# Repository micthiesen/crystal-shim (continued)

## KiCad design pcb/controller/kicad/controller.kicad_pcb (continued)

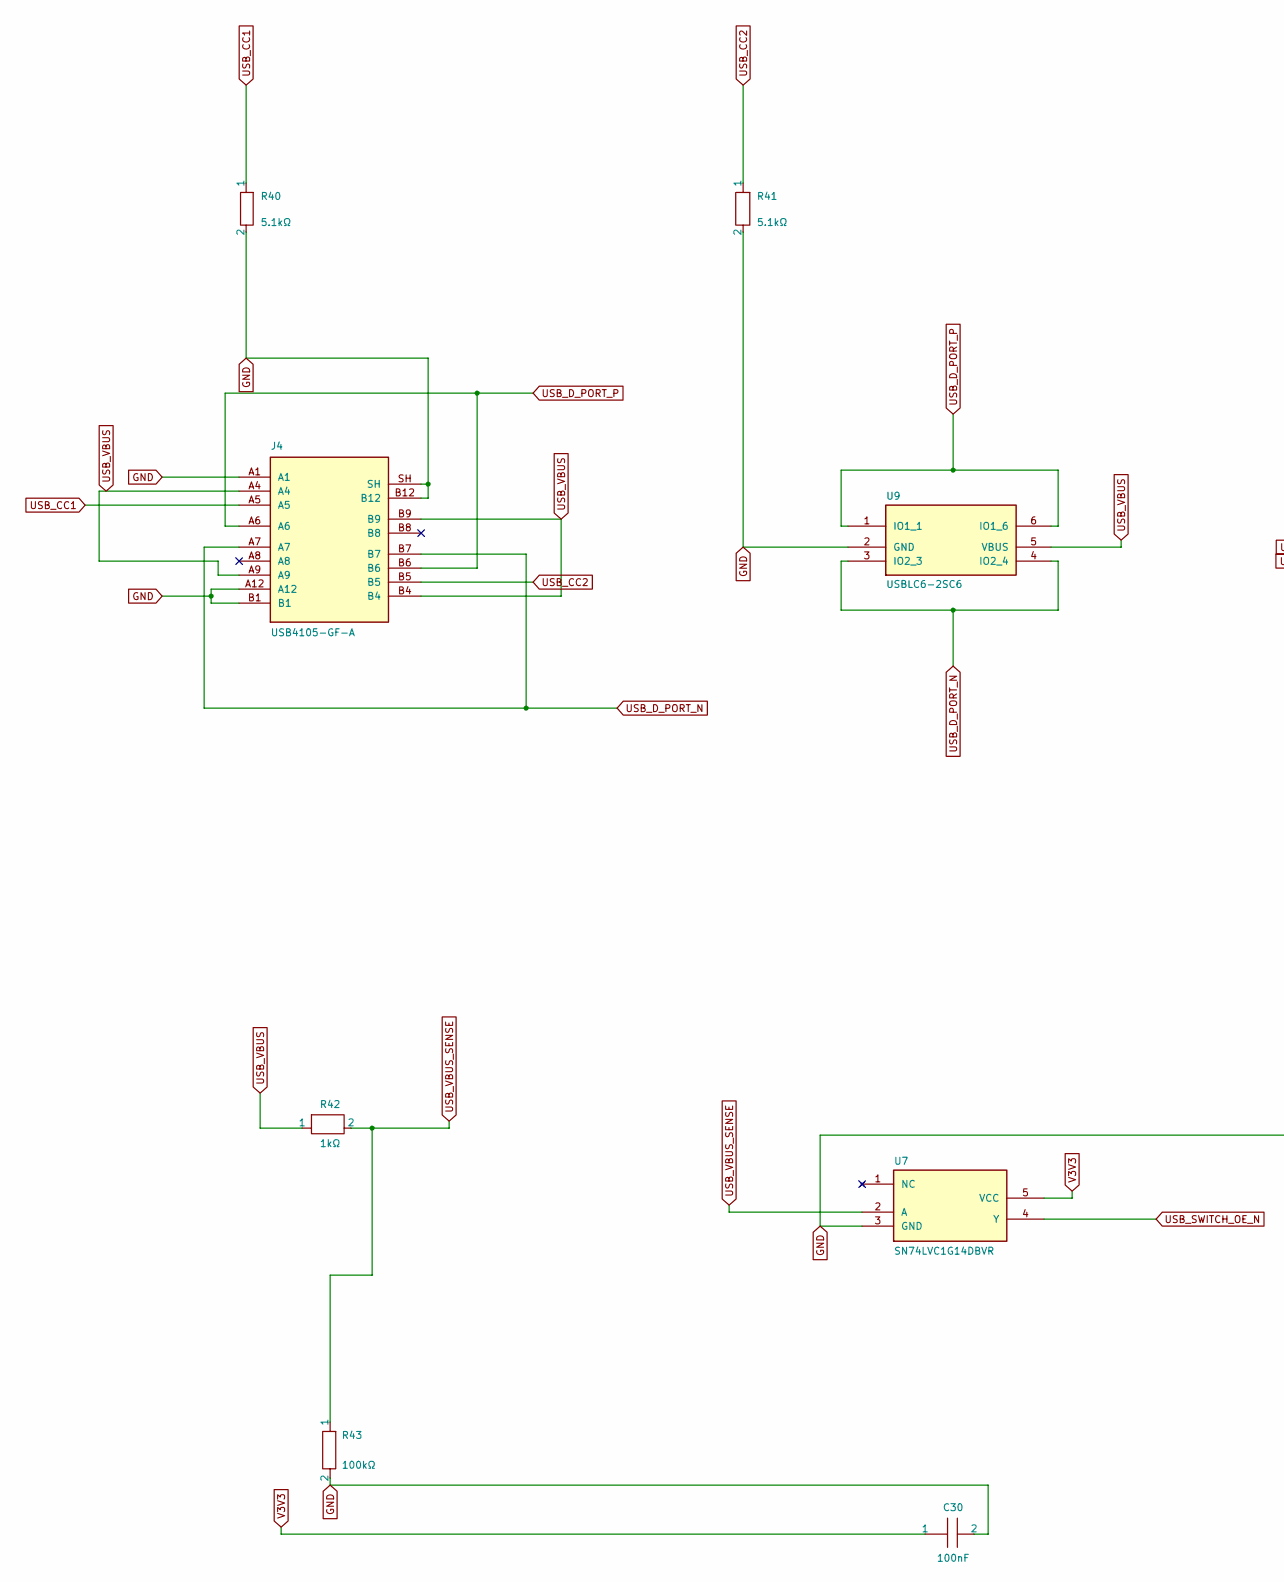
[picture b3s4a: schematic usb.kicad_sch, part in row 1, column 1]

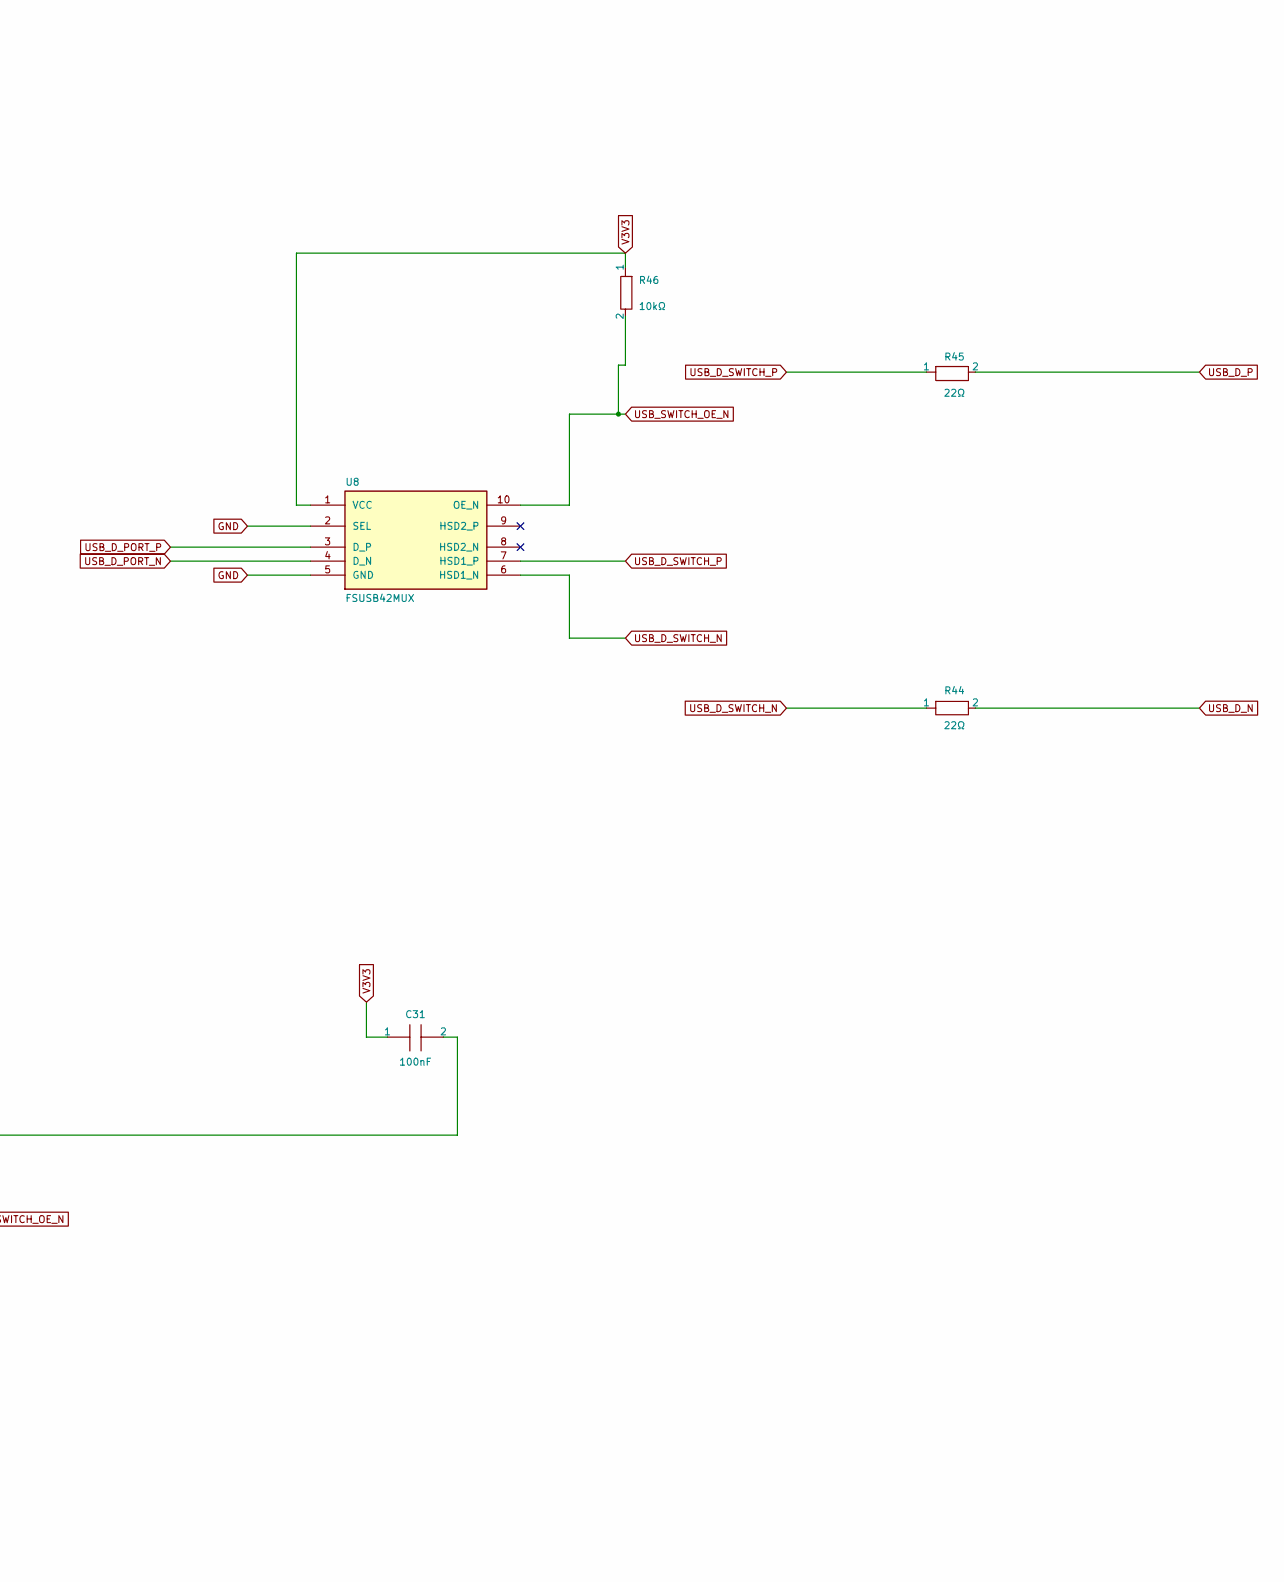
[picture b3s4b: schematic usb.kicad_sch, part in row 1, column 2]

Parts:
C30: 100nF; Controller_C30; MPN C1608X7R1H104K080AA
C31: 100nF; Controller_C31; MPN C1608X7R1H104K080AA
J4: USB4105-GF-A; Controller_J4; MPN USB4105-GF-A
R40: 5.1kΩ; Controller_R40; MPN ERJ3EKF5101V
R41: 5.1kΩ; Controller_R41; MPN ERJ3EKF5101V
R42: 1kΩ; Controller_R42; MPN ERJ3EKF1001V
R43: 100kΩ; Controller_R43; MPN ERJ3EKF1003V
R44: 22Ω; Controller_R44; MPN ERJ3EKF22R0V
R45: 22Ω; Controller_R45; MPN ERJ3EKF22R0V
R46: 10kΩ; Controller_R46; MPN ERJ3EKF1002V
U7: SN74LVC1G14DBVR; Controller_U7; MPN SN74LVC1G14DBVR
U8: FSUSB42MUX; Controller_U8; MPN FSUSB42MUX
U9: USBLC6-2SC6; Controller_U9; MPN USBLC6-2SC6

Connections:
GND: C30.2, C31.2, J4.A1, J4.A12, J4.B1, J4.B12, J4.SH, R40.2, R41.2, R43.2, U7.3 (GND), U8.2 (SEL), U8.5 (GND), U9.2 (GND); also elsewhere on the board
USB_CC1: J4.A5, R40.1
USB_CC2: J4.B5, R41.1
USB_D_N: R44.2; also elsewhere on the board
USB_D_P: R45.2; also elsewhere on the board
USB_D_PORT_N: J4.A7, J4.B7, U8.4 (D_N), U9.3 (IO2_3), U9.4 (IO2_4)
USB_D_PORT_P: J4.A6, J4.B6, U8.3 (D_P), U9.1 (IO1_1), U9.6 (IO1_6)
USB_D_SWITCH_N: R44.1, U8.6 (HSD1_N)
USB_D_SWITCH_P: R45.1, U8.7 (HSD1_P)
USB_SWITCH_OE_N: R46.2, U7.4 (Y), U8.10 (OE_N)
USB_VBUS: J4.A4, J4.A9, J4.B4, J4.B9, R42.1, U9.5 (VBUS)
USB_VBUS_SENSE: R42.2, R43.1, U7.2 (A)
V3V3: C30.1, C31.1, R46.1, U7.5 (VCC), U8.1 (VCC); also elsewhere on the board

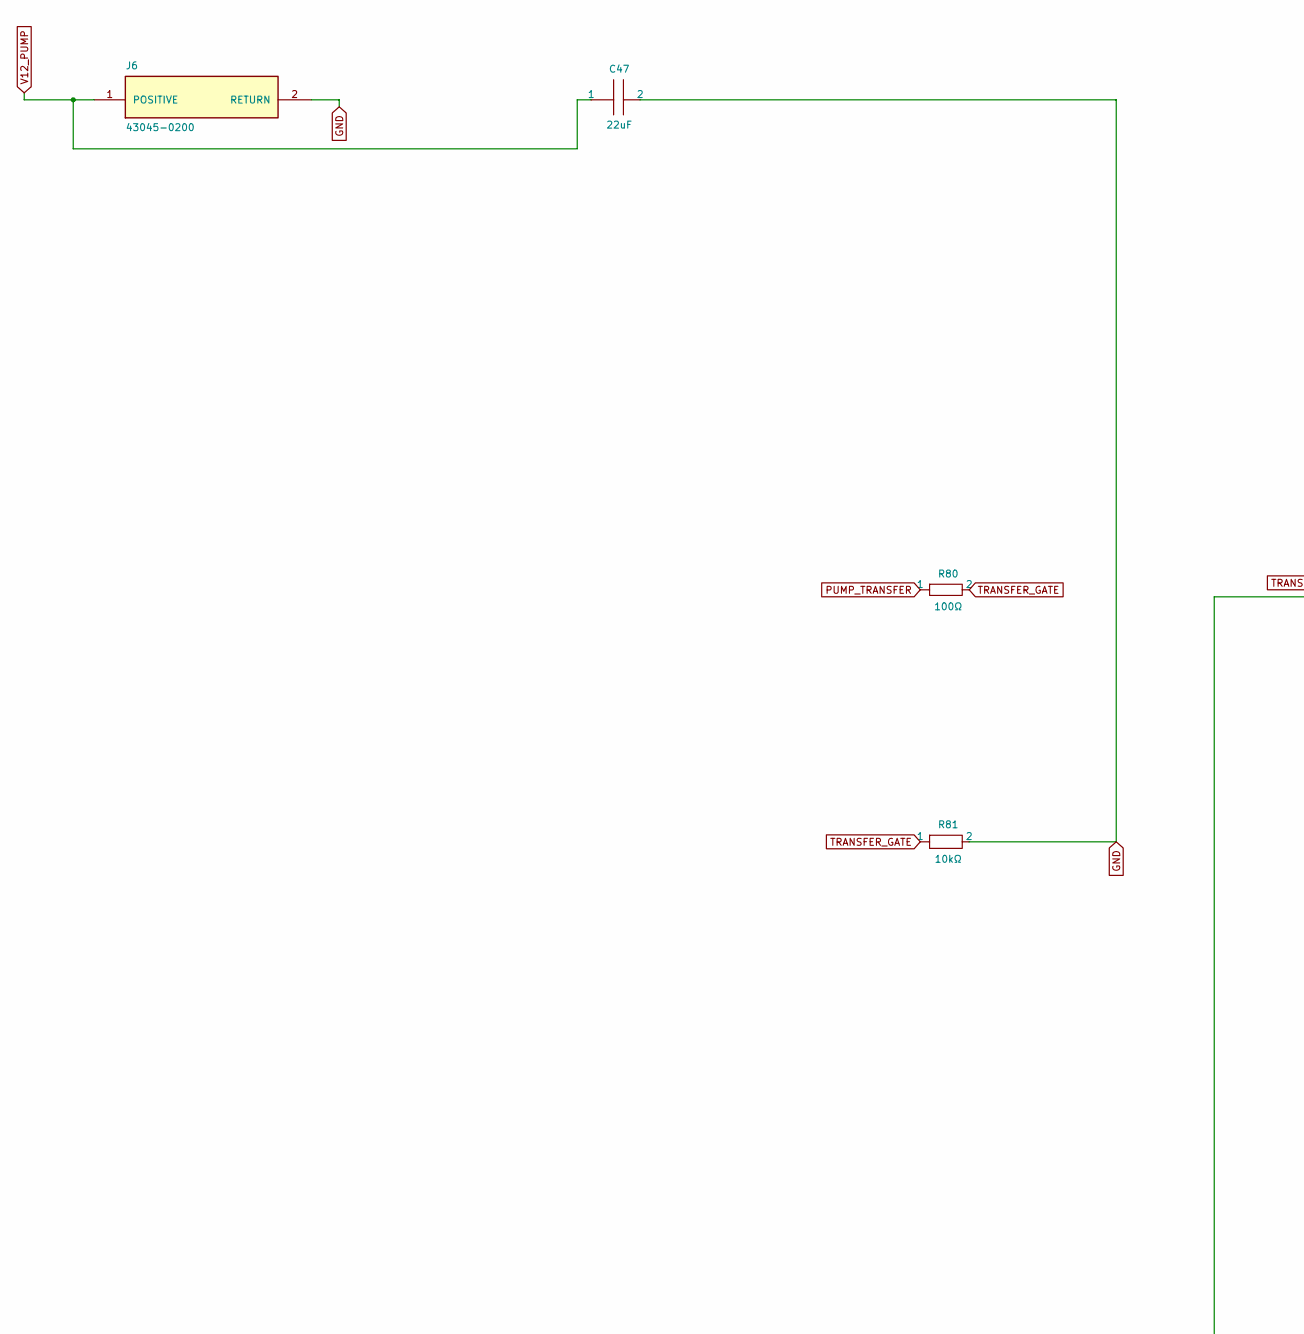
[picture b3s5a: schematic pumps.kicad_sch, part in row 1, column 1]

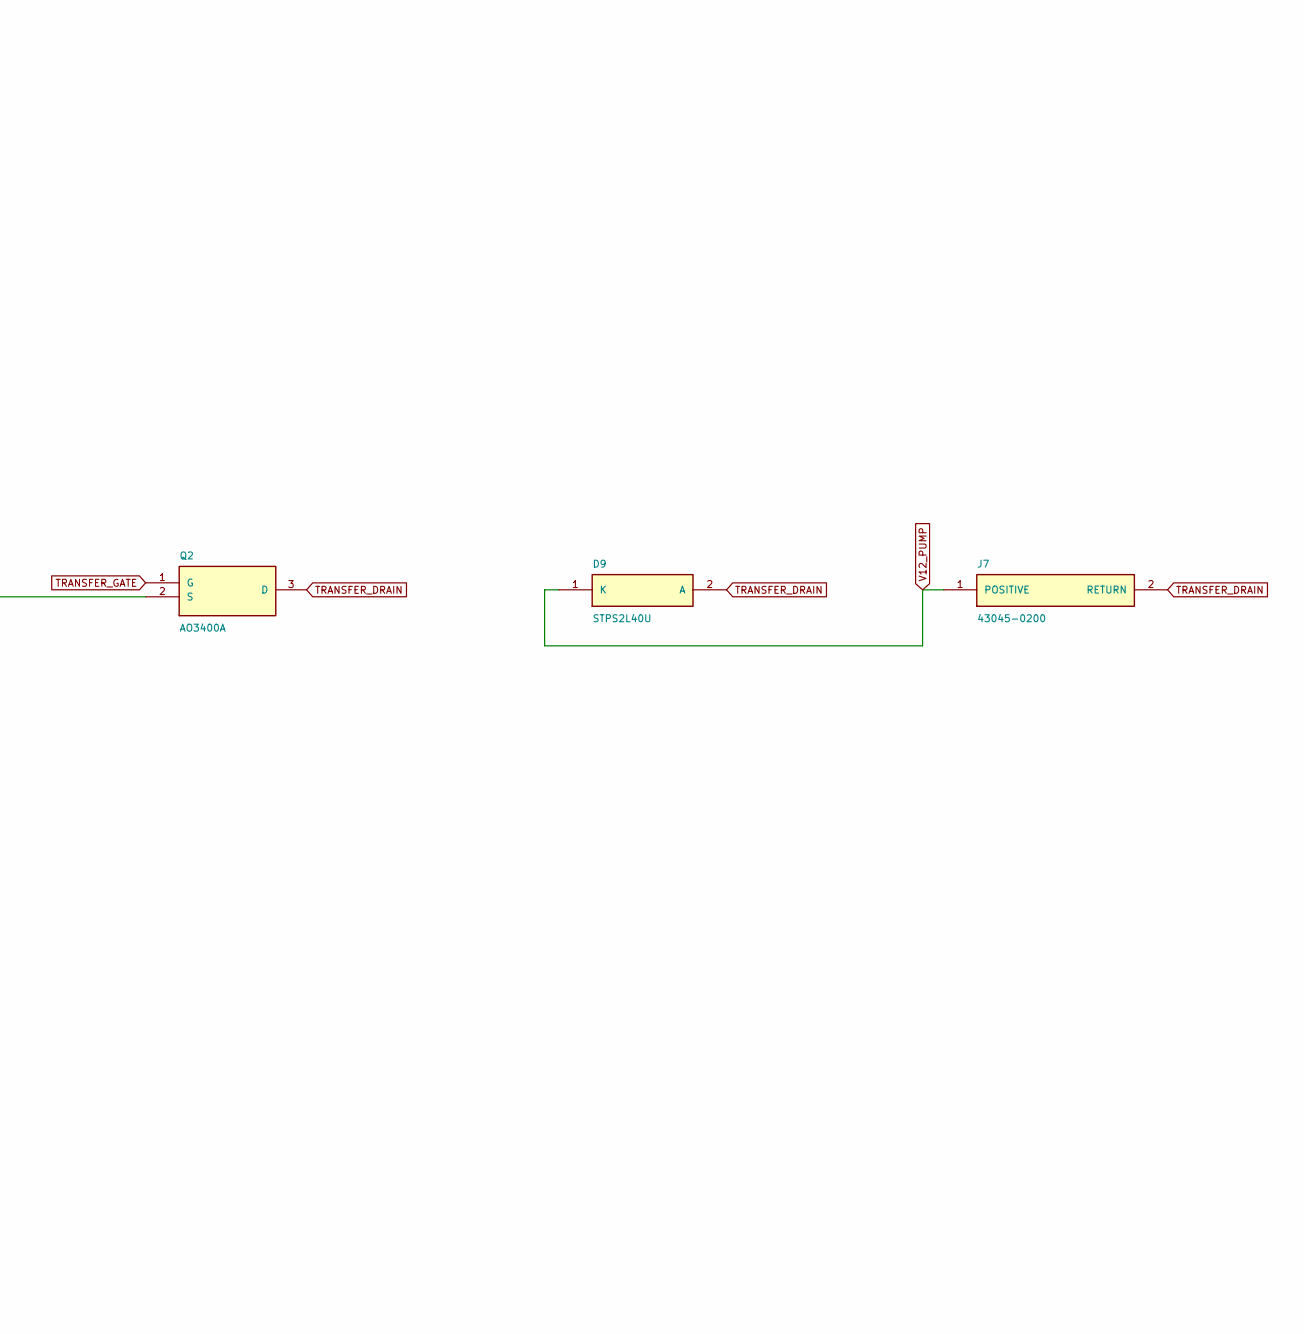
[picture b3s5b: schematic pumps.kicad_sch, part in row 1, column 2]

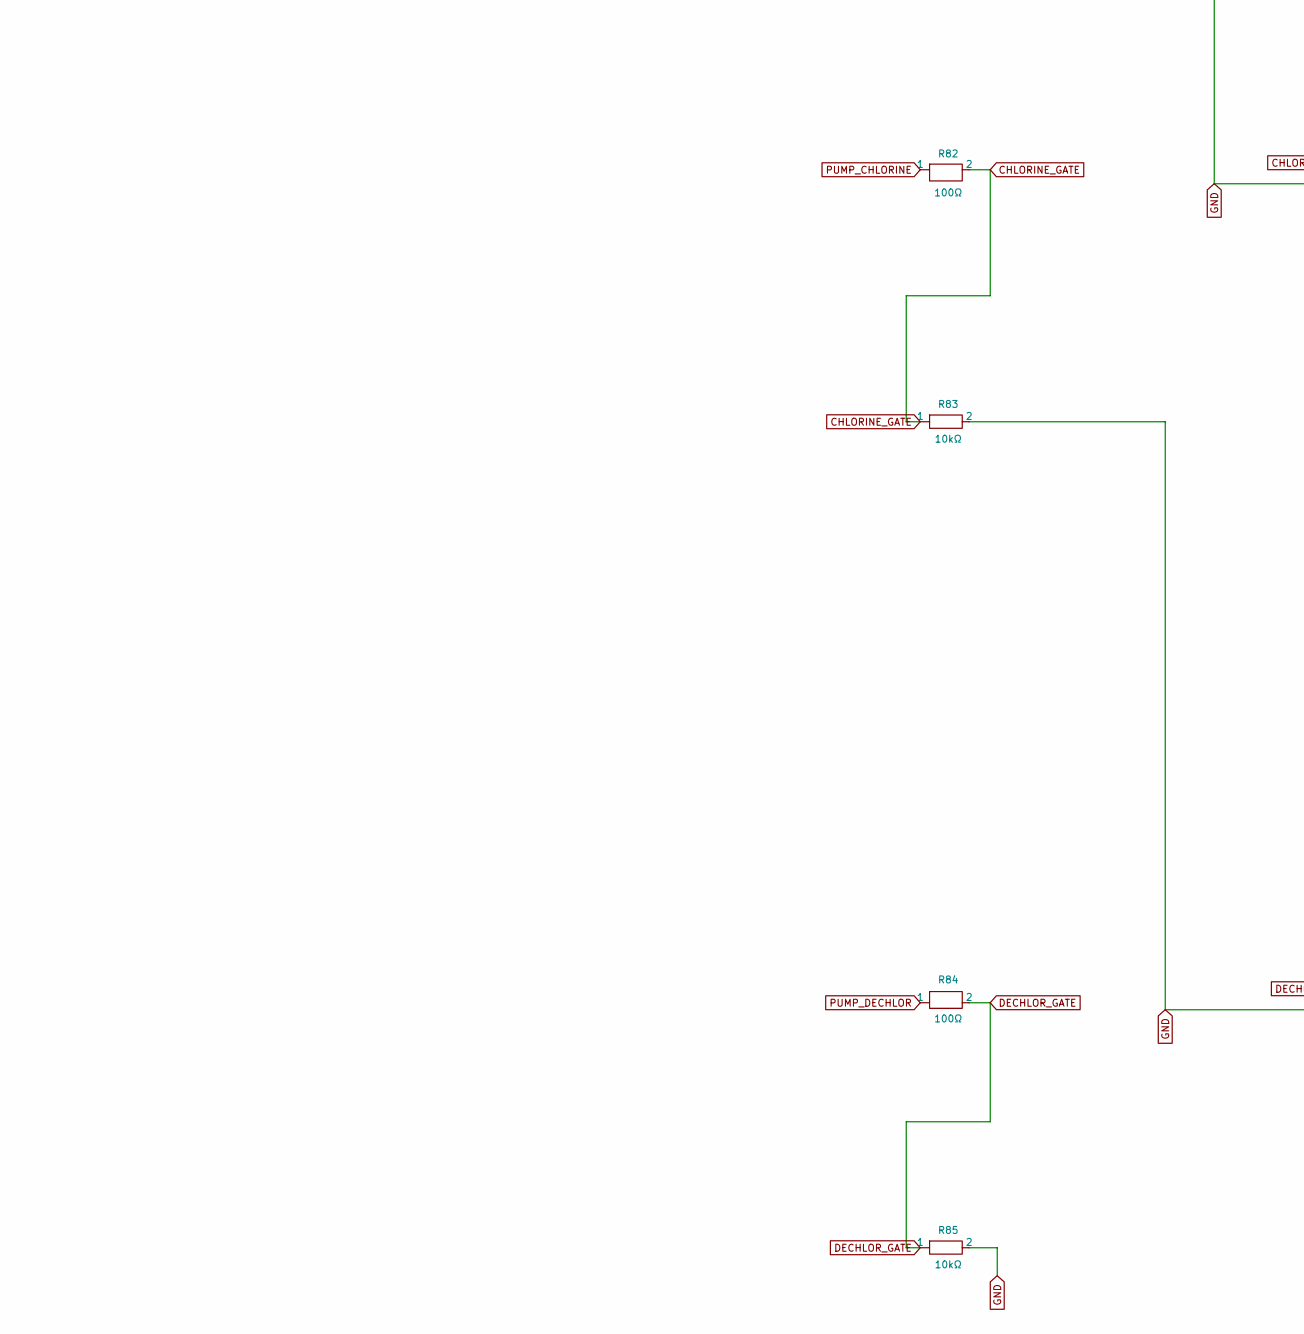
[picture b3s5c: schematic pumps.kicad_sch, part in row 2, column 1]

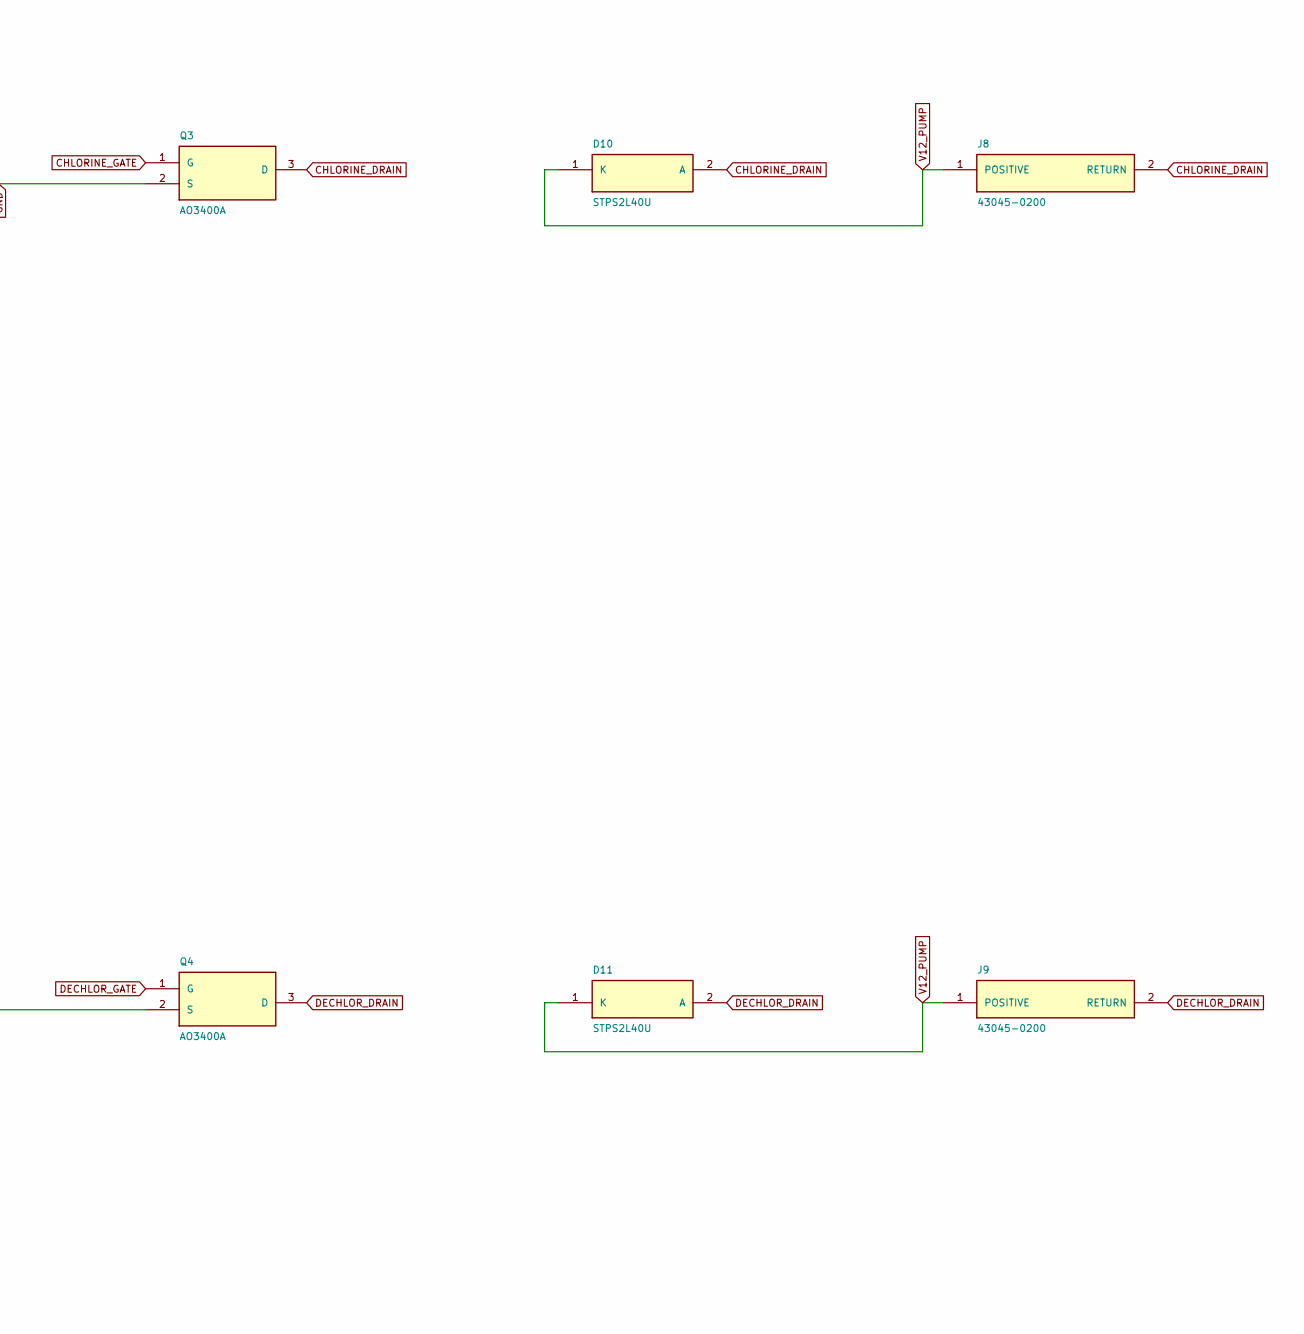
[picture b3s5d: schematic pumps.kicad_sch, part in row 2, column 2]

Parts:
C47: 22uF; Controller_C47; MPN GRM32ER71E226ME15L
D9: STPS2L40U; Controller_D9; MPN STPS2L40U
D10: STPS2L40U; Controller_D10; MPN STPS2L40U
D11: STPS2L40U; Controller_D11; MPN STPS2L40U
J6: 43045-0200; Controller_J6; MPN 43045-0200
J7: 43045-0200; Controller_J7; MPN 43045-0200
J8: 43045-0200; Controller_J8; MPN 43045-0200
J9: 43045-0200; Controller_J9; MPN 43045-0200
Q2: AO3400A; Controller_Q2; MPN AO3400A
Q3: AO3400A; Controller_Q3; MPN AO3400A
Q4: AO3400A; Controller_Q4; MPN AO3400A
R80: 100Ω; Controller_R80; MPN ERJ3EKF1000V
R81: 10kΩ; Controller_R81; MPN ERJ3EKF1002V
R82: 100Ω; Controller_R82; MPN ERJ3EKF1000V
R83: 10kΩ; Controller_R83; MPN ERJ3EKF1002V
R84: 100Ω; Controller_R84; MPN ERJ3EKF1000V
R85: 10kΩ; Controller_R85; MPN ERJ3EKF1002V

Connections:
CHLORINE_DRAIN: D10.2 (A), J8.2 (RETURN), Q3.3 (D)
CHLORINE_GATE: Q3.1 (G), R82.2, R83.1
DECHLOR_DRAIN: D11.2 (A), J9.2 (RETURN), Q4.3 (D)
DECHLOR_GATE: Q4.1 (G), R84.2, R85.1
GND: C47.2, J6.2 (RETURN), Q2.2 (S), Q3.2 (S), Q4.2 (S), R81.2, R83.2, R85.2; also elsewhere on the board
PUMP_CHLORINE: R82.1; also elsewhere on the board
PUMP_DECHLOR: R84.1; also elsewhere on the board
PUMP_TRANSFER: R80.1; also elsewhere on the board
TRANSFER_DRAIN: D9.2 (A), J7.2 (RETURN), Q2.3 (D)
TRANSFER_GATE: Q2.1 (G), R80.2, R81.1
V12_PUMP: C47.1, D9.1 (K), D10.1 (K), D11.1 (K), J6.1 (POSITIVE), J7.1 (POSITIVE), J8.1 (POSITIVE), J9.1 (POSITIVE)

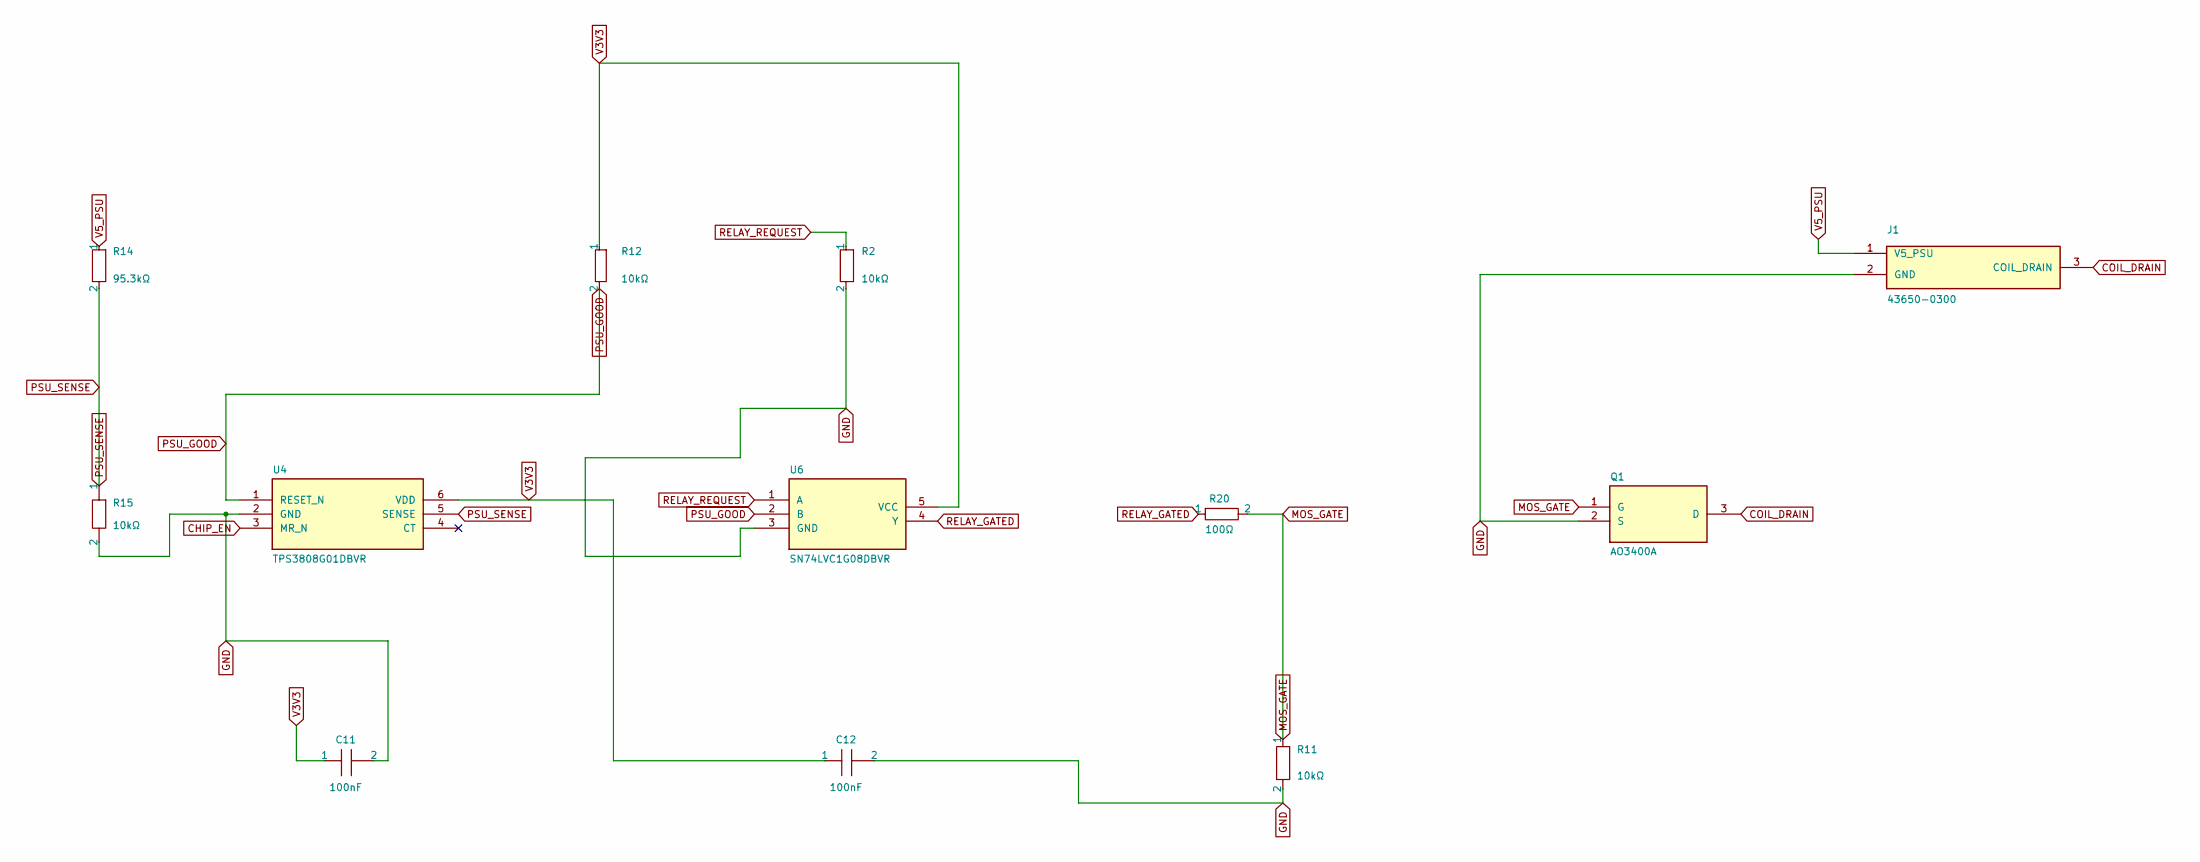
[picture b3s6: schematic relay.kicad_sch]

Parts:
C11: 100nF; Controller_C11; MPN C1608X7R1H104K080AA
C12: 100nF; Controller_C12; MPN C1608X7R1H104K080AA
J1: 43650-0300; Controller_J1; MPN 43650-0300
Q1: AO3400A; Controller_Q1; MPN AO3400A
R2: 10kΩ; Controller_R2; MPN ERJ3EKF1002V
R11: 10kΩ; Controller_R11; MPN ERJ3EKF1002V
R12: 10kΩ; Controller_R12; MPN ERJ3EKF1002V
R14: 95.3kΩ; Controller_R14; MPN ERA3AEB9532V
R15: 10kΩ; Controller_R15; MPN ERA3AEB103V
R20: 100Ω; Controller_R20; MPN ERJ3EKF1000V
U4: TPS3808G01DBVR; Controller_U4; MPN TPS3808G01DBVR
U6: SN74LVC1G08DBVR; Controller_U6; MPN SN74LVC1G08DBVR

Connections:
CHIP_EN: U4.3 (MR_N); also elsewhere on the board
COIL_DRAIN: J1.3 (COIL_DRAIN), Q1.3 (D)
GND: C11.2, C12.2, J1.2 (GND), Q1.2 (S), R2.2, R11.2, R15.2, U4.2 (GND), U6.3 (GND); also elsewhere on the board
MOS_GATE: Q1.1 (G), R11.1, R20.2
PSU_GOOD: R12.2, U4.1 (RESET_N), U6.2 (B); also elsewhere on the board
PSU_SENSE: R14.2, R15.1, U4.5 (SENSE)
RELAY_GATED: R20.1, U6.4 (Y); also elsewhere on the board
RELAY_REQUEST: R2.1, U6.1 (A); also elsewhere on the board
V3V3: C11.1, C12.1, R12.1, U4.6 (VDD), U6.5 (VCC); also elsewhere on the board
V5_PSU: J1.1 (V5_PSU), R14.1; also elsewhere on the board

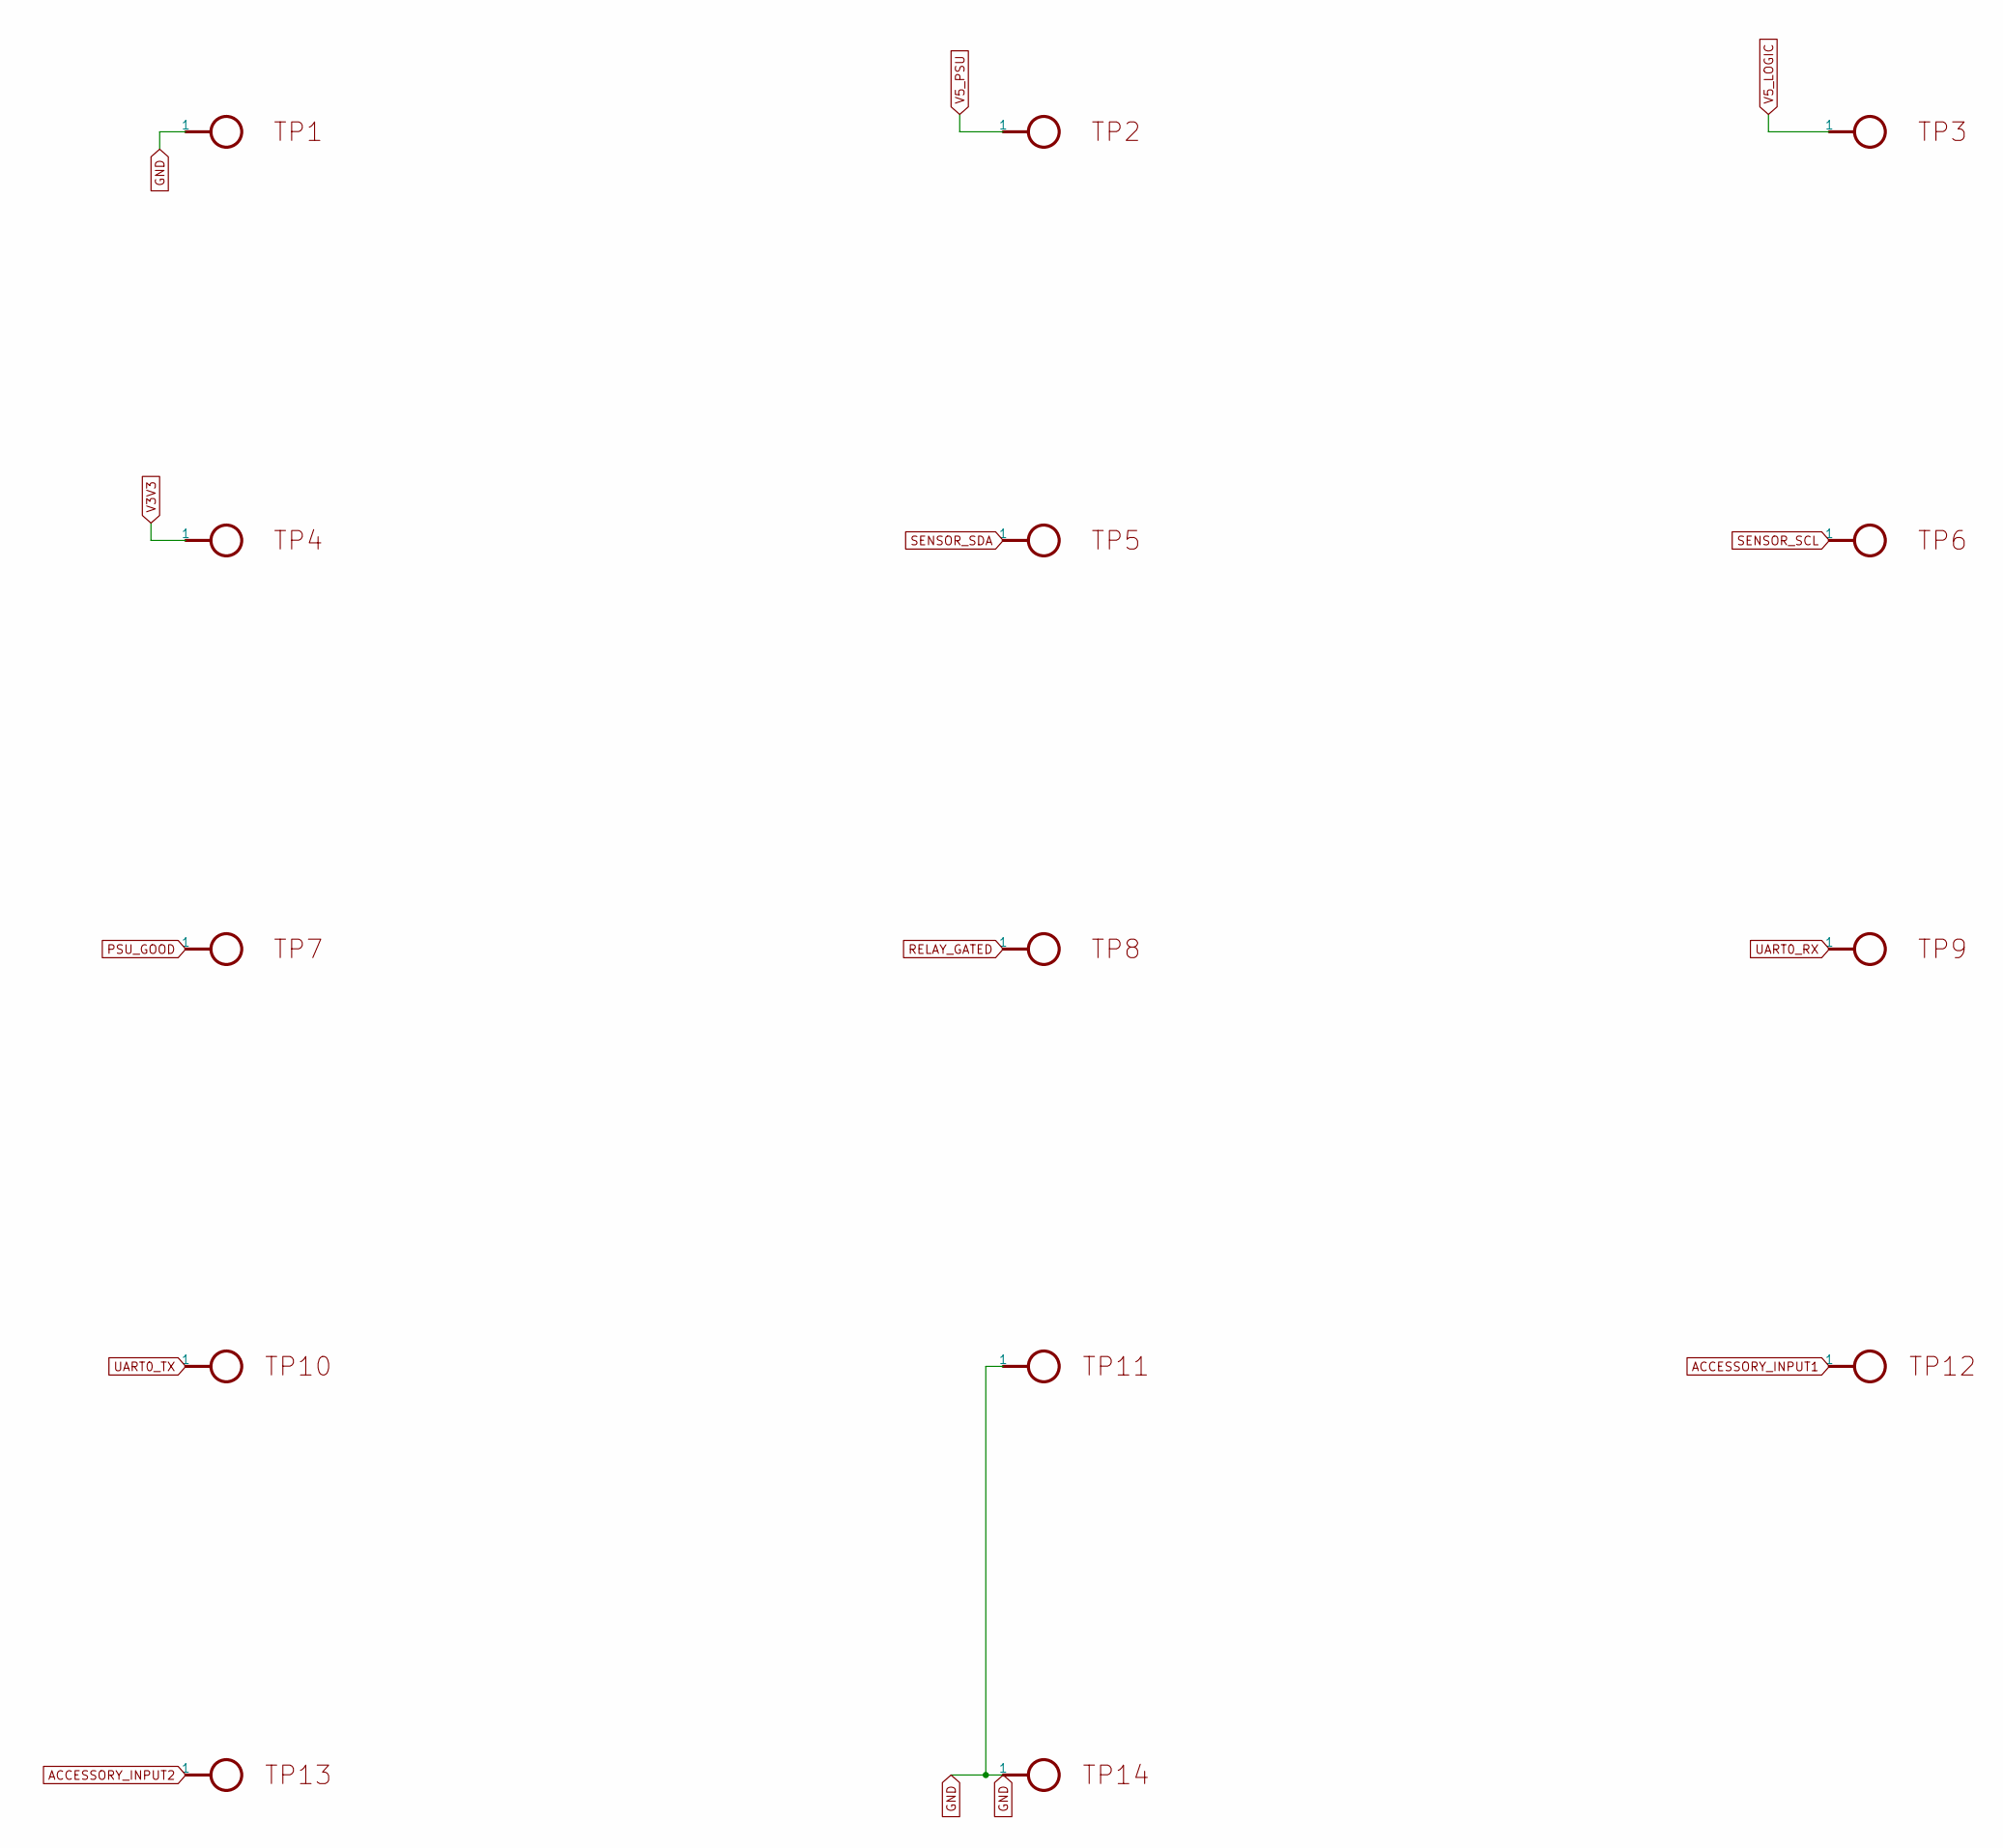
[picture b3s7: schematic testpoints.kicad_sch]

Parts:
TP1: TP1; Controller_TP1
TP2: TP2; Controller_TP2
TP3: TP3; Controller_TP3
TP4: TP4; Controller_TP4
TP5: TP5; Controller_TP5
TP6: TP6; Controller_TP6
TP7: TP7; Controller_TP7
TP8: TP8; Controller_TP8
TP9: TP9; Controller_TP9
TP10: TP10; Controller_TP10
TP11: TP11; Controller_TP11
TP12: TP12; Controller_TP12
TP13: TP13; Controller_TP13
TP14: TP14; Controller_TP14

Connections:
ACCESSORY_INPUT1: TP12.1; also elsewhere on the board
ACCESSORY_INPUT2: TP13.1; also elsewhere on the board
GND: TP1.1, TP11.1, TP14.1; also elsewhere on the board
PSU_GOOD: TP7.1; also elsewhere on the board
RELAY_GATED: TP8.1; also elsewhere on the board
SENSOR_SCL: TP6.1; also elsewhere on the board
SENSOR_SDA: TP5.1; also elsewhere on the board
UART0_RX: TP9.1; also elsewhere on the board
UART0_TX: TP10.1; also elsewhere on the board
V3V3: TP4.1; also elsewhere on the board
V5_LOGIC: TP3.1; also elsewhere on the board
V5_PSU: TP2.1; also elsewhere on the board

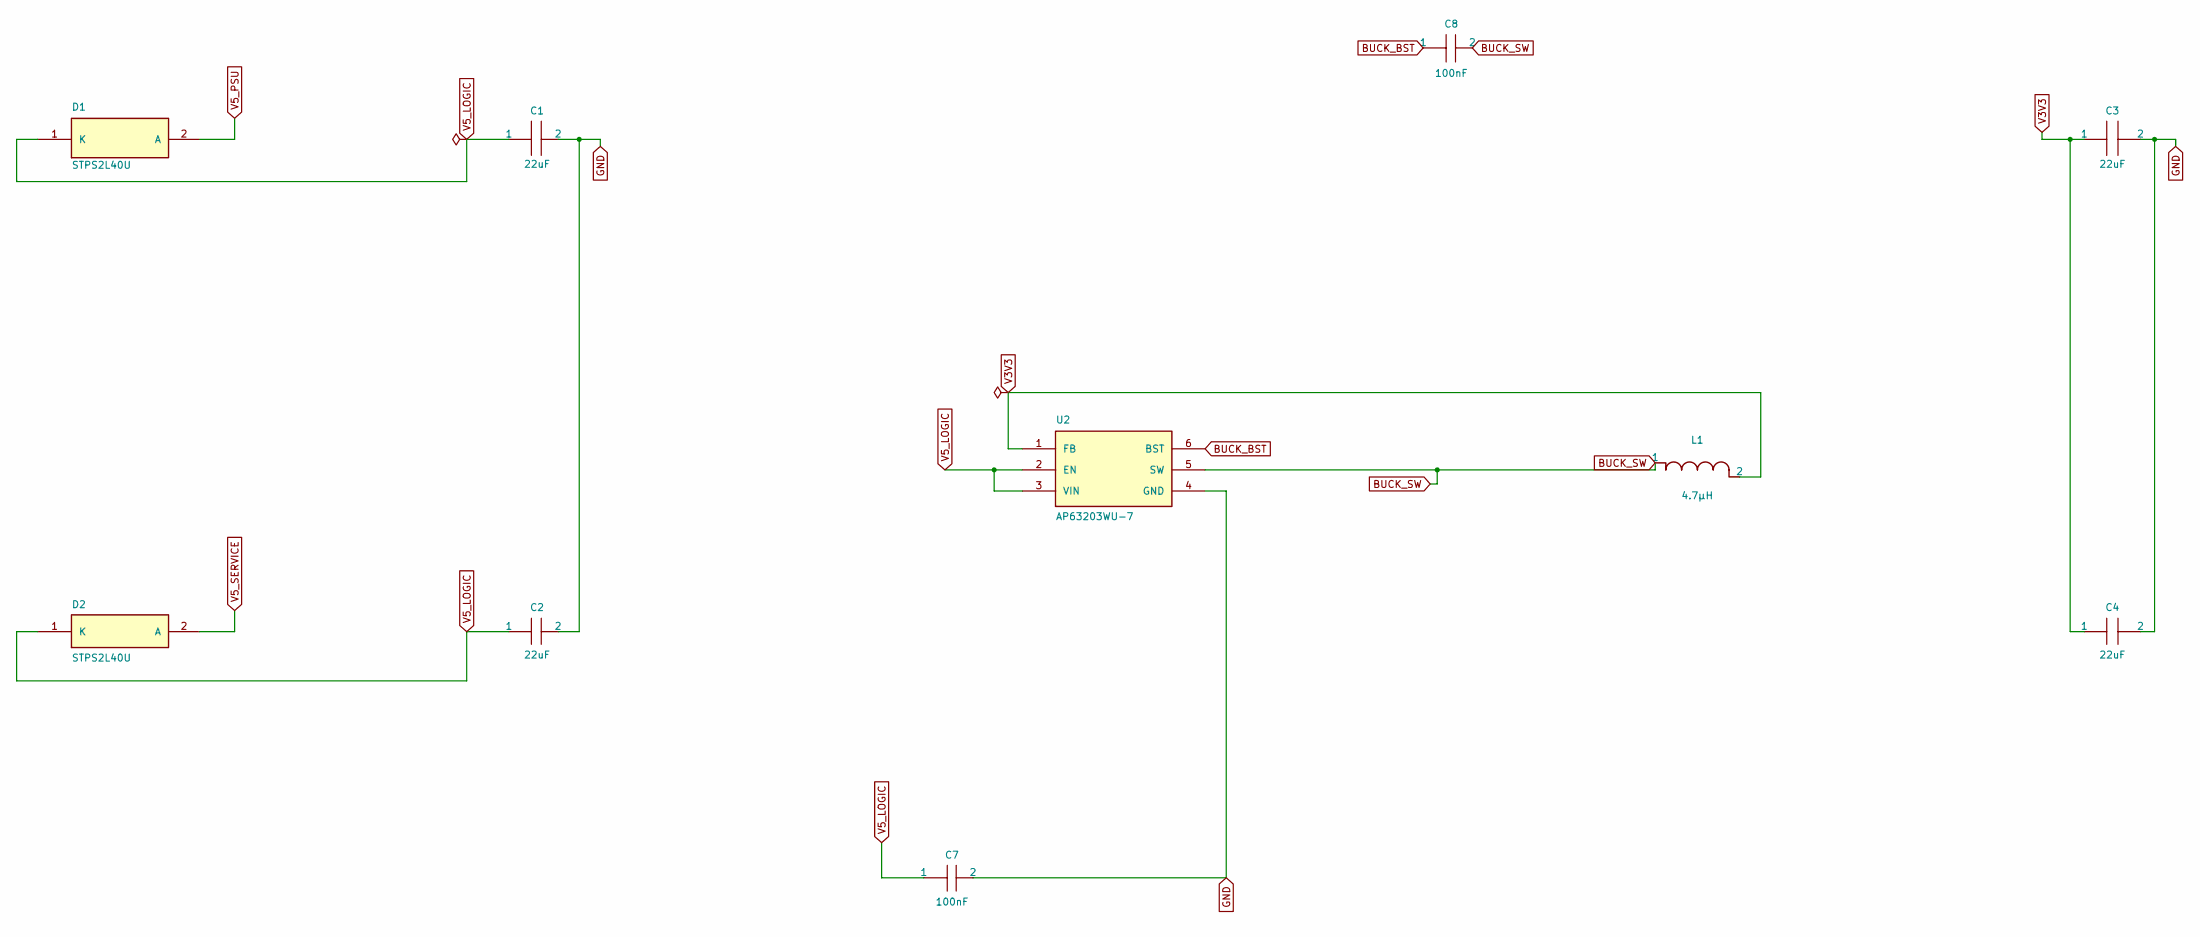
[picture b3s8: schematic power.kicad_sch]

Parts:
C1: 22uF; Controller_C1; MPN GRM32ER71E226ME15L
C2: 22uF; Controller_C2; MPN GRM32ER71E226ME15L
C3: 22uF; Controller_C3; MPN GRM32ER71E226ME15L
C4: 22uF; Controller_C4; MPN GRM32ER71E226ME15L
C7: 100nF; Controller_C7; MPN C1608X7R1H104K080AA
C8: 100nF; Controller_C8; MPN C1608X7R1H104K080AA
D1: STPS2L40U; Controller_D1; MPN STPS2L40U
D2: STPS2L40U; Controller_D2; MPN STPS2L40U
L1: 4.7µH; Controller_L1; MPN SRP5030TA-4R7M
U2: AP63203WU-7; Controller_U2; MPN AP63203WU-7

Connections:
BUCK_BST: C8.1, U2.6 (BST)
BUCK_SW: C8.2, L1.1, U2.5 (SW)
GND: C1.2, C2.2, C3.2, C4.2, C7.2, U2.4 (GND); also elsewhere on the board
V3V3: C3.1, C4.1, L1.2, U2.1 (FB); also elsewhere on the board
V5_LOGIC: C1.1, C2.1, C7.1, D1.1 (K), D2.1 (K), U2.2 (EN), U2.3 (VIN); also elsewhere on the board
V5_PSU: D1.2 (A); also elsewhere on the board
V5_SERVICE: D2.2 (A); also elsewhere on the board
